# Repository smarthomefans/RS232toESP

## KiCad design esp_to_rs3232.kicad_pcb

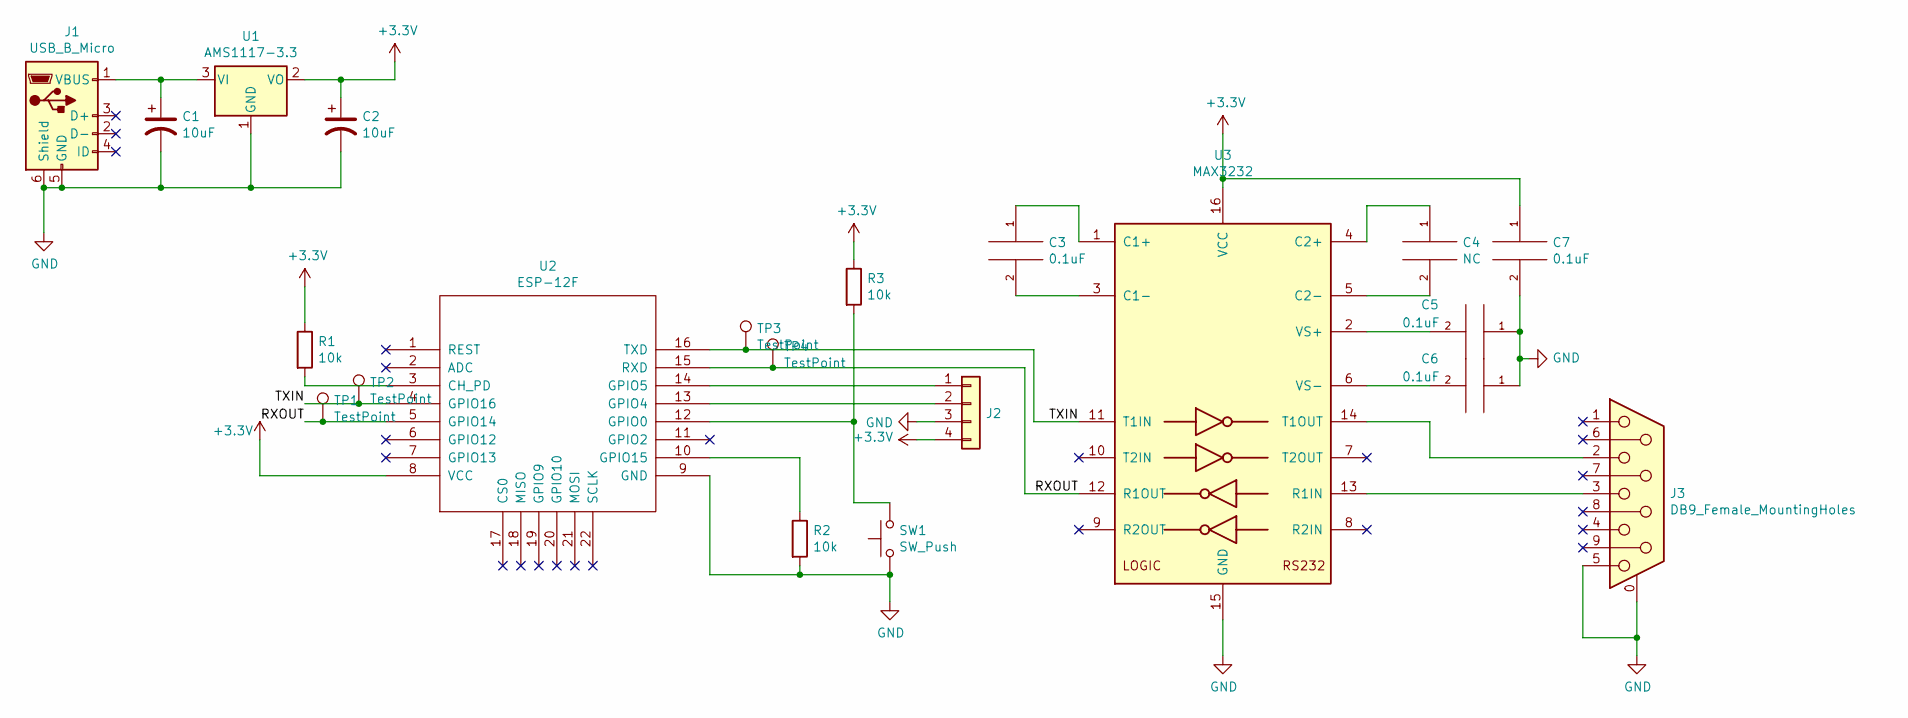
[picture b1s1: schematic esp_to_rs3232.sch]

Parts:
C1, C2: 10uF; CP_EIA-3216-18_Kemet-A_Pad1.58x1.35mm_HandSolder
C3, C5, C6, C7: 0.1uF; C_0603_1608Metric_Pad1.05x0.95mm_HandSolder
C4: NC; C_0603_1608Metric
J1: USB_B_Micro; USB_Micro-B_Molex_47346-0001
J2: Conn_01x04; PinHeader_1x04_P2.54mm_Vertical
J3: DB9_Female_MountingHoles; DSUB-9_Female_Horizontal_P2.77x2.84mm_EdgePinOffset4.94mm_H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
R1, R2, R3: 10k; R_0603_1608Metric_Pad1.05x0.95mm_HandSolder
SW1: SW_Push; SW_SPST_PTS810
TP1, TP2, TP3, TP4: TestPoint; TestPoint_Bridge_Pitch2.0mm_Drill0.7mm
U1: AMS1117-3.3; SOT-223-3_TabPin2
U2: ESP-12F; ESP-12E_SMD
U3: MAX3232; TSSOP-16_4.4x5mm_P0.65mm

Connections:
+3V3: C2.1, C7.1, J2.4, R1.1, R3.1, U1.2 (VO), U2.8 (VCC), U3.16 (VCC)
/RXOUT: TP1.1, TP4.1, U2.5 (GPIO14), U2.15 (RXD), U3.12 (R1OUT)
/TXIN: TP2.1, TP3.1, U2.4 (GPIO16), U2.16 (TXD), U3.11 (T1IN)
GND: C1.2, C2.2, C5.1, C6.1, C7.2, J1.5 (GND), J1.6 (Shield), J2.3, J3.0 (PAD), J3.5, R2.2, SW1.1, U1.1 (GND), U2.9 (GND), U3.15 (GND)
unnamed: C1.1, J1.1 (VBUS), U1.3 (VI)
unnamed: C3.1, U3.1 (C1+)
unnamed: C3.2, U3.3 (C1-)
unnamed: C4.1, U3.4 (C2+)
unnamed: C4.2, U3.5 (C2-)
unnamed: C5.2, U3.2 (VS+)
unnamed: C6.2, U3.6 (VS-)
unnamed: J2.1, U2.14 (GPIO5)
unnamed: J2.2, U2.13 (GPIO4)
unnamed: J3.2, U3.14 (T1OUT)
unnamed: J3.3, U3.13 (R1IN)
unnamed: R1.2, U2.3 (CH_PD)
unnamed: R2.1, U2.10 (GPIO15)
unnamed: R3.2, SW1.2, U2.12 (GPIO0)

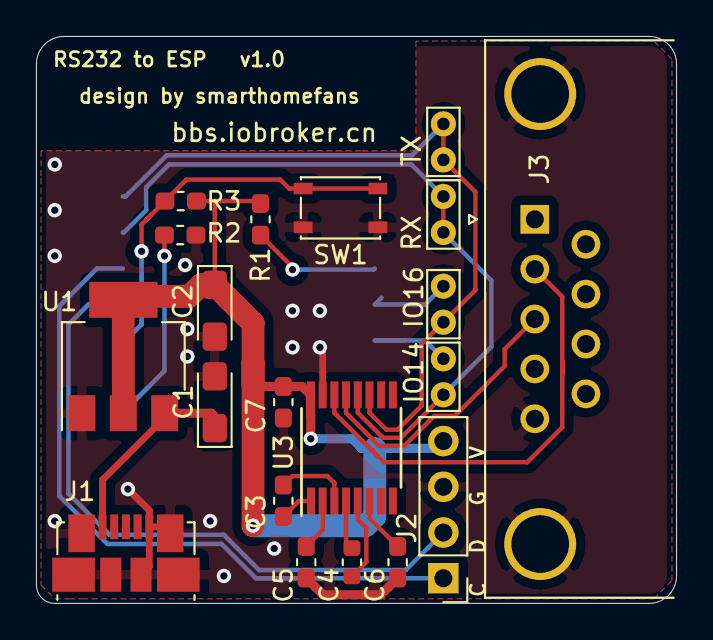
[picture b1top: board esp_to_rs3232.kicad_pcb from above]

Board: 2 copper layers, 35.6 x 31.5 mm, 21 parts (1 on the bottom side), 18 nets.

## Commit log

2019-09-13 Version 1.0
2019-09-16 Add datasheets
2019-09-16 update footprint
2019-09-21 change c2 value
